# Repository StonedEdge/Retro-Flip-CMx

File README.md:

<h1 align="center">Retro-Flip-CMx</h1>

Stay tuned... dual screen flip handheld? Or something like that. Upgrades over the Retro Lite CM5 will include:

- Analog triggers via RP2350B and hall sensors
- BQ25792 with dual power path support for VBUS input (or maybe just keep using BQ24292i)
- TPS65988D (for 2 USB-C ports) - one port supports USB 3.0, OTG and DP. Other port supports USB 2.0 and PD
- USB hub for dual USB-C ports
- Hall sensor for lid switch
- Better analog sticks (not switch sticks) - 3DS sliders. Rear back buttons for L3/R3
- Custom heatpipe plus finstack
- Button for entering maskrom mode for programming eMMC
- Two screens (OLED 1080p, 480p bottom display)
- Two 3DS XL hinges
- Blackberry 8250 finger IR touchpad
- Hotkeys
- Gyro
- RK3588 Compute Module or similar

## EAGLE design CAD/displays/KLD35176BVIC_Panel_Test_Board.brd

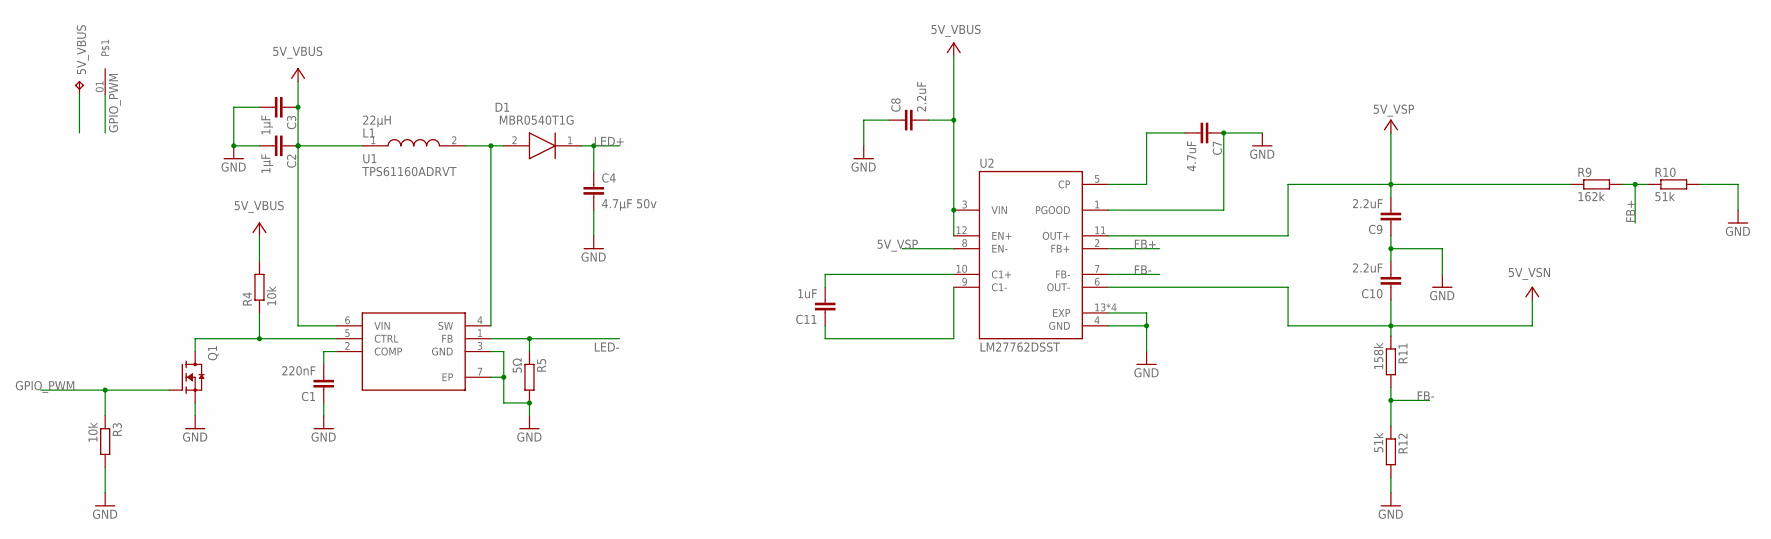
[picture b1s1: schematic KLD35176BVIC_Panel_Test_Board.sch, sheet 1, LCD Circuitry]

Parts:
5V_VBUS: TPTP19R; TP19R
C1: 220nF; C0603
C2, C3: 1µF; C0603
C4: 4.7µF 50v; C0805
C7: 4.7uF; C0603
C8, C9, C10: 2.2uF; C0603
C11: 1uF; C0603
D1: MBR0540T1G; SOD3716X135N
L1: 22µH; VLCF4020_1
Q1: AO3400A; SOT95P280X125-3N
R3, R4: 10k; R0603
R5: 5Ω; R0603
R9: 162k; R0603
R10, R12: 51k; R0603
R11: 158k; R0603
U1: TPS61160ADRVT; SON65P200X200X80-7N
U2: LM27762DSST; IC_LM27762DSST
U$1: PAD; AMPHENOL_10129381-908001BLF

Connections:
5V_VBUS: 5V_VBUS.TP, C2.1, C3.1, C8.2, L1.1, R4.2, U1.6 (VIN), U2.3 (VIN), U2.12 (EN+); also elsewhere on the board
5V_VSN: C10.1, R11.1, U2.6 (OUT-); also elsewhere on the board
5V_VSP: C9.2, R9.1, U2.8 (EN-), U2.11 (OUT+); also elsewhere on the board
FB+: R9.2, R10.1, U2.2 (FB+)
FB-: R11.2, R12.1, U2.7 (FB-)
GND: C1.1, C2.2, C3.2, C4.2, C7.1, C8.1, C9.1, C10.2, Q1.2 (S), R3.2, R5.2, R10.2, R12.2, U1.3 (GND), U1.7 (EP), U2.1 (PGOOD), U2.4 (GND), U2.13 (EXP), U2.14 (EXP), U2.15 (EXP), U2.16 (EXP); also elsewhere on the board
GPIO_PWM: Q1.1 (G), R3.1, U$1.01
LED+: C4.1, D1.1 (K); also elsewhere on the board
LED-: R5.1, U1.1 (FB); also elsewhere on the board
unnamed: C1.2, U1.2 (COMP)
unnamed: D1.2 (A), L1.2, U1.4 (SW)
unnamed: C7.2, U2.5 (CP)
unnamed: C11.2, U2.10 (C1+)
unnamed: C11.1, U2.9 (C1-)
unnamed: Q1.3 (D), R4.1, U1.5 (CTRL)

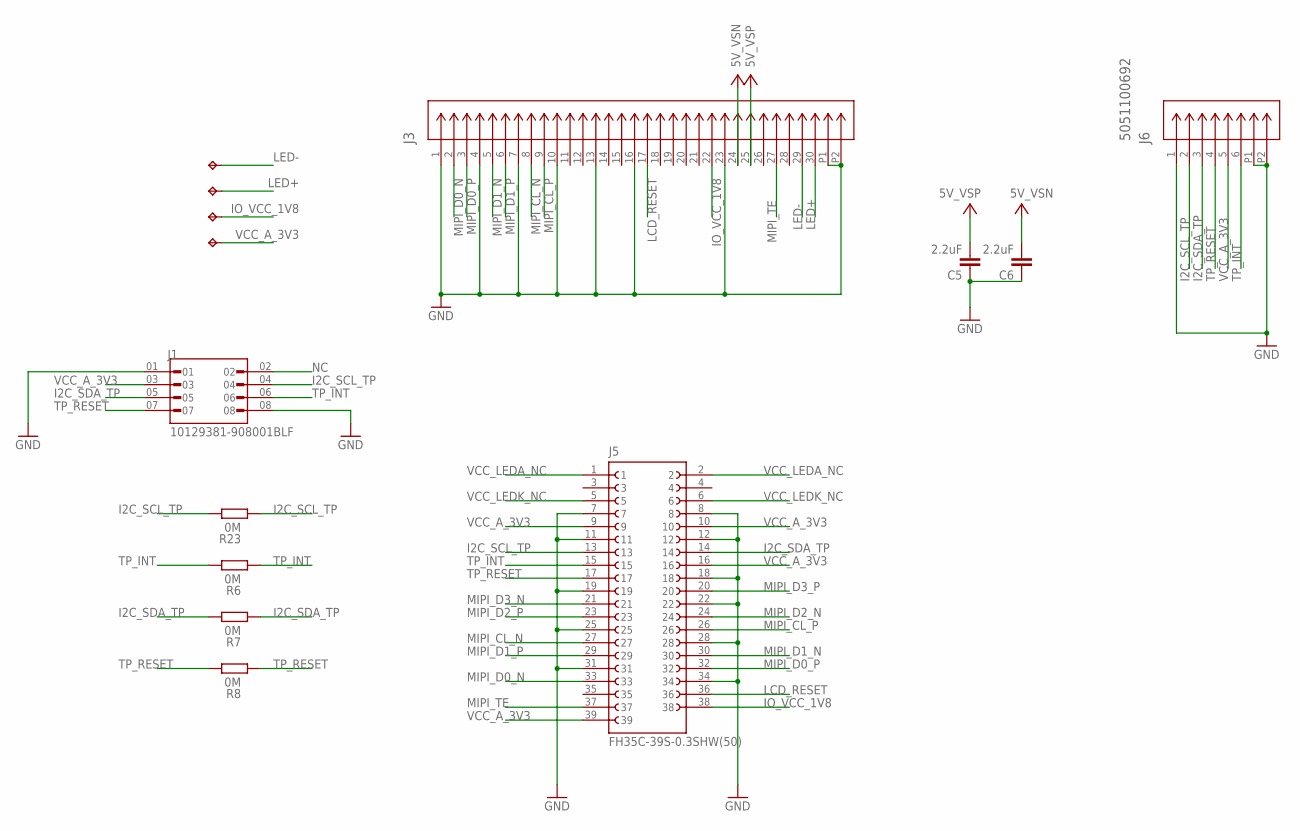
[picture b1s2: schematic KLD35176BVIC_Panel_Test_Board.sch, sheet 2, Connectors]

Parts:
C5, C6: 2.2uF; C0603
IO_VCC_1V8: TPTP19R; TP19R
J1: 10129381-908001BLF; AMPHENOL_10129381-908001BLF
J3: 5051103091; CON_5051103091_MOL
J5: FH35C-39S-0.3SHW(50); HRS_FH35C-39S-0.3SHW(50)
J6: 5051100692; CON_5051100692_MOL
LED+: TPTP19R; TP19R
LED-: TPTP19R; TP19R
R6, R7, R8, R23: 0M; R0402
VCC_A_3V3: TPTP19R; TP19R

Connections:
5V_VSN: C6.2, J3.24; also elsewhere on the board
5V_VSP: C5.2, J3.25; also elsewhere on the board
GND: C5.1, C6.1, J1.01, J1.08, J3.1, J3.4, J3.7, J3.10, J3.13, J3.16, J3.23, J3.P1, J3.P2, J5.7, J5.8, J5.11, J5.12, J5.18, J5.19, J5.22, J5.25, J5.28, J5.31, J5.34, J6.1, J6.P1, J6.P2; also elsewhere on the board
I2C_SCL_TP: J1.04, J5.13, J6.2, R23.1, R23.2
I2C_SDA_TP: J1.05, J5.14, J6.3, R7.1, R7.2
IO_VCC_1V8: IO_VCC_1V8.TP, J3.22, J5.38
LCD_RESET: J3.17, J5.36
LED+: J3.30, LED+.TP; also elsewhere on the board
LED-: J3.29, LED-.TP; also elsewhere on the board
MIPI_CL_N: J3.8, J5.27
MIPI_CL_P: J3.9, J5.26
MIPI_D0_N: J3.2, J5.33
MIPI_D0_P: J3.3, J5.32
MIPI_D1_N: J3.5, J5.30
MIPI_D1_P: J3.6, J5.29
MIPI_D2_N: J5.24
MIPI_D2_P: J5.23
MIPI_D3_N: J5.21
MIPI_D3_P: J5.20
MIPI_TE: J3.27, J5.37
NC: J1.02
TP_INT: J1.06, J5.15, J6.6, R6.1, R6.2
TP_RESET: J1.07, J5.17, J6.4, R8.1, R8.2
VCC_A_3V3: J1.03, J5.9, J5.10, J5.16, J5.39, J6.5, VCC_A_3V3.TP
VCC_LEDA_NC: J5.1, J5.2
VCC_LEDK_NC: J5.5, J5.6

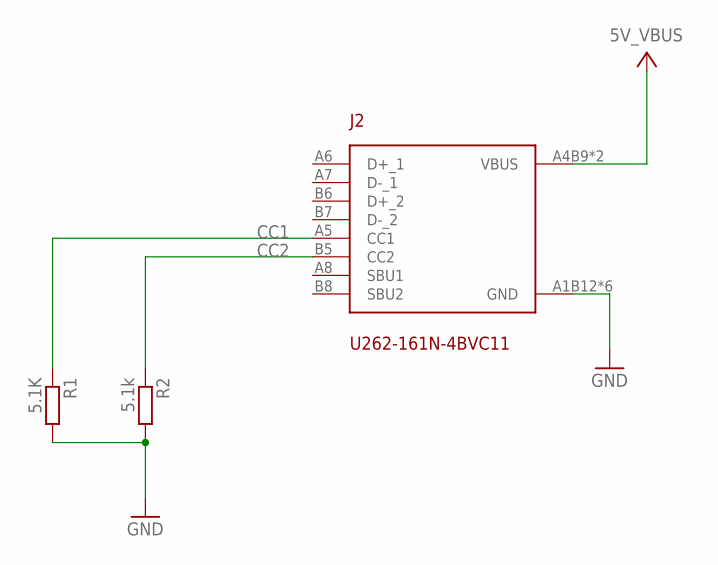
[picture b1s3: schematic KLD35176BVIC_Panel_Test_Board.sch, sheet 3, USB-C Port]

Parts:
J2: U262-161N-4BVC11
R1: 5.1K; R0603
R2: 5.1k; R0603

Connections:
5V_VBUS: J2.A4B9 (VBUS), J2.B4A9 (VBUS); also elsewhere on the board
CC1: J2.A5 (CC1), R1.1
CC2: J2.B5 (CC2), R2.1
GND: J2.A1B12 (GND), J2.B1A12 (GND), J2.SHIELD_1 (GND), J2.SHIELD_2 (GND), J2.SHIELD_3 (GND), J2.SHIELD_4 (GND), R1.2, R2.2; also elsewhere on the board

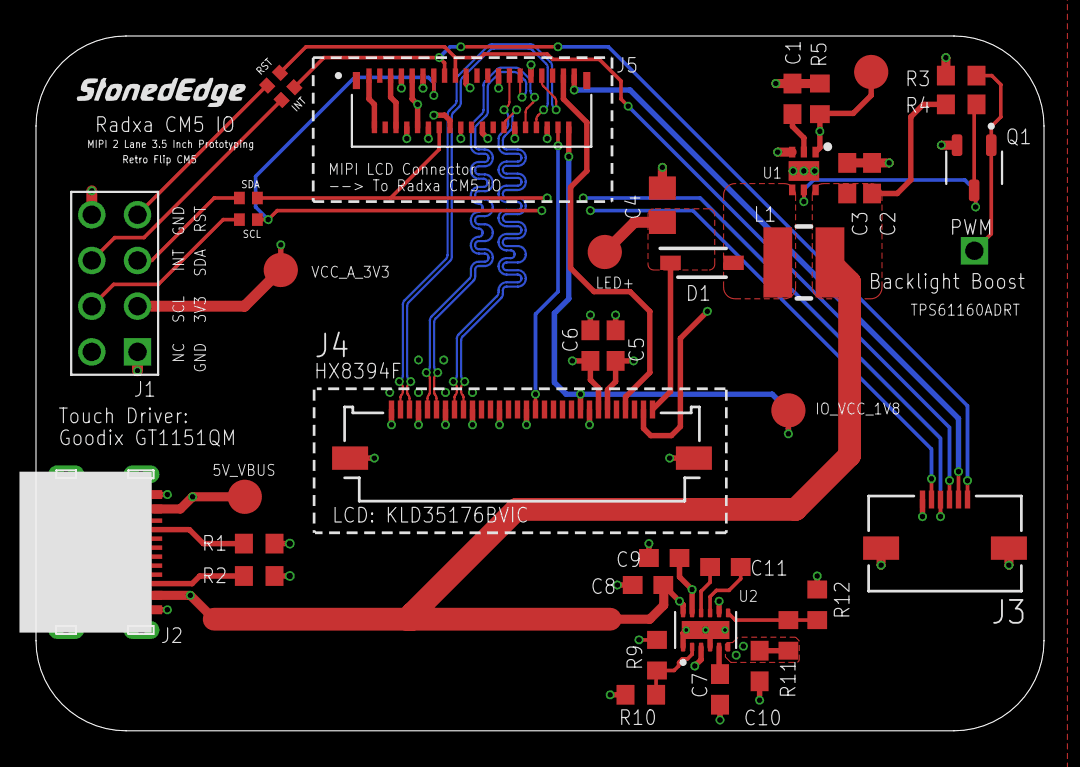
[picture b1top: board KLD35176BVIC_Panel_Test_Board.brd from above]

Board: 4 copper layers, 56.0 x 38.6 mm, 40 parts (0 on the bottom side), 33 nets.

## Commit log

2026-02-03 Add 5.5 inch display connector
2026-02-03 Add 5.5 inch display datasheet
2026-02-05 Upload 3.5inch connectors
2026-02-06 Upload 3DS connector models (0.12mm mating thickness)
2026-02-06 3.5inch touch display connector (bottom contact)
2026-02-08 Upload BB8520 trackpad mating connector
2026-04-28 Upload 5v regulator datasheet
2026-04-28 Upload rp2350 design guide
2026-04-30 Upload test panel PCB
2026-05-25 DXQ4D1603_1280x960 4.16"
    Add 4.16 inch 4:3 panel
2026-05-25 6 inch OLED datasheet
2026-05-30 Upload 4.16 inch 1280x960 + 1920 x 1080 6inch OLED
2026-05-30 Upload basic housing form
2026-05-31 Upload 7 inch OLED panel datasheet
2026-06-01 Update project name and hardware specifications
2026-06-01 Upload Switch 2 speakers
2026-06-01 Upload various buttons

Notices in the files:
parts and their libraries:
COPYRIGHT: Copyright (C) 2023 Ultra Librarian. All rights reserved.
COPYRIGHT: Copyright (C) 2026 Ultra Librarian. All rights reserved.
